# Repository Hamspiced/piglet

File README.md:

# Piglet Wardriver

**Piglet** is an open-source ESP32-based wardriving platform that scans nearby Wi-Fi networks, records GPS position, saves WiGLE-compatible CSV logs to SD, and provides a real-time web UI for control, uploads, and device status.

Designed for **[Seeed XIAO ESP32-S3](https://wiki.seeedstudio.com/xiao_esp32s3_getting_started/), [XIAO ESP32-C5](https://wiki.seeedstudio.com/xiao_esp32c5_getting_started/), [XIAO ESP32-C6](https://wiki.seeedstudio.com/xiao_esp32c6_getting_started/), and [XIAO ESP32-C3](https://wiki.seeedstudio.com/XIAO_ESP32C3_Getting_Started/)**, Piglet focuses on:

- Reliable scanning while in motion  
- Clean WiGLE-ready data collection  
- Simple field deployment  
- Fully hackable open firmware

## Features

- 2.4 GHz Wi-Fi scanning  
- 5 GHz scanning on ESP32-C5 hardware  
- GPS position, heading, and speed logging  
- SD card logging in WiGLE CSV format  
- Web UI for:
  - Start / stop scanning  
  - Upload logs to WiGLE, WDGoWars, and Wardrift  
  - View device status  
  - Manage SD files  
  - Edit configuration  
- OLED live status display  
- Optional battery monitoring (board dependent)  
- Automatic STA connect with AP fallback  
- **Home network auto-return** — detects your home SSID while wardriving, automatically connects and uploads pending CSVs, then resumes wardriving once you drive out of range again
- Optimized for mobile wardriving or warWalking!
- **ESP-Now Mesh Node mode** — pair with a coordinator device for multi-node wardriving
- **Mesh auto-start on boot** — configure `meshModeOnBoot` to automatically enter Core or Node mode after uploads complete, bypassing the AP window
- **Screen rotation** — mount the display upside-down and set `rotateScreen180=true` to flip 180°
- **Auto-start wardriving after uploads** — set `autoStartAfterUpload=true` to disconnect from home Wi-Fi immediately after boot uploads complete and begin scanning without delay
- **PigletNode** — standalone minimal firmware for XIAO ESP32-C5 that boots directly as a mesh node (no display, GPS, or SD required)
- **Wardrive Go BLE bridge** — while on the Mesh Node/Core page, advertise a RocketGod "iosESP" BLE bridge so the Wardrive Go / WarBLE Go phone app can pair and plot APs live on its map
- **Self-update from GitHub Releases** — checks for a newer firmware version at boot and, with one click in the Web UI, downloads and flashes it over the air
- **Core-pushed mesh node OTA updates** — a Piglet acting as Core can push a new firmware image to any connected node (PigletNode, T-Dongle C5, or headless XIAO) over the existing ESP-Now link, no USB required
- **On-device "Update Nodes through Core?" prompt** — a Core's own screen shows a 30-second confirm prompt when a connected XIAO-based node is running mismatched firmware; a single button press confirms the push
- **Auto-update for headless PigletNode nodes** — optional toggle lets a Core silently push firmware to out-of-date headless PigletNode nodes with no on-device confirmation
- **Manual per-node channel-range overrides** — pin a specific mesh node (by MAC) to a fixed channel range from the Web UI instead of the automatic even split

## ESP-Now Mesh Network Node Mode

Piglet includes a built-in **Mesh Node mode** that lets it act as a wireless wardriving node alongside a compatible coordinator device. In this mode, Piglet scans Wi-Fi networks and forwards results over ESP-Now — no SD card or GPS fix required on Piglet itself. The coordinator handles GPS stamping and data logging.

### Compatible Coordinator Devices

- **Biscuit Pro** by [Hedge / Biscuit Shop](https://biscuitshop.us)
- **JCMK C5 Wardriver** by JustCallMeKoko

### How to Use

1. Power on your coordinator device (Biscuit Pro or JCMK C5 Wardriver)
2. On Piglet, press the button to cycle pages until you reach **Mesh Node** (the last page after the pig animation)
3. Piglet automatically searches for a coordinator on ESP-Now channel 6
4. Once connected, it receives a channel range assignment and begins forwarding scan data
5. Press the button again to exit Mesh Node mode and return to normal wardriving

### Mesh Node Display

While in Mesh Node mode the OLED shows:
- Link status (Searching / Core linked)
- Coordinator MAC address
- Assigned channel range
- Total networks discovered
- Records forwarded to the coordinator

> **Note:** Entering Mesh Node mode suspends normal WiGLE CSV logging. All data is sent live to the coordinator. Exiting the page restores normal scanning automatically.

### Auto-Start Mesh Mode on Boot

Set `meshModeOnBoot` in `/wardriver.cfg` to automatically enter mesh mode after boot uploads are complete, without needing to navigate pages manually:

| Value | Behaviour |
|-------|-----------|
| `none` | Normal wardriving (default) |
| `core` | Enters Mesh Core mode — acts as coordinator, logs records from nodes |
| `node` | Enters Mesh Node mode — forwards scan results to a Core |

When `core` or `node` is set the SoftAP window is **skipped entirely** (ESP-Now owns the WiFi stack and the AP would be non-functional). The device goes straight from boot uploads to the mesh page. Set via the web UI **Mesh Mode On Boot** dropdown or directly in `/wardriver.cfg`.

### Wardrive Go BLE Bridge

While on the Mesh Node or Core page, Piglet can advertise a RocketGod "iosESP" BLE bridge (service UUID `47686F73-7445-5350-4272-696467655376`, advertised as `iosESP-XXXX`) so the **Wardrive Go / WarBLE Go** phone app can pair and plot APs live on its map:

- **Node** pushes its own scan finds plus its own GPS fix.
- **Core** pushes every node-forwarded AP plus its own GPS fix.

Enable it with the **Wardrive Go BLE Bridge** toggle in the Web UI's Configuration card (`wardriveGoBridge` in `/wardriver.cfg`, default off). The bridge is only ever active while on the Mesh Node/Core page — it is torn down immediately when you leave it. While enabled, the Mesh page's hold-button hint is replaced with a `WG: off / advertising / connected` status line. Requires the **NimBLE-Arduino** library (see Building Firmware below).

## PigletNode — Standalone Mesh Node

A minimal, standalone firmware for the **Seeed XIAO ESP32-C5** in the `PigletNode/` folder. No display, GPS, or SD card required — flash it and it automatically pairs with any Piglet running in Core mode and begins scanning.

- Single-file Arduino sketch, zero external library dependencies
- Boots directly into JCMK-compatible ESP-Now node mode
- Dual-band scanning: 40 channels (2.4 GHz ch 1–14 + 5 GHz UNII-1/2/2e/3)
- Auto-pairs with Piglet Core mode (XIAO or T-Dongle)
- 30-second Core timeout with automatic re-search
- LED: fast blink = searching, slow blink = paired and scanning
- Hold BOOT button > 2 s to force a re-search

**Flash:** Open `PigletNode/PigletNode.ino` in Arduino IDE, select **XIAO_ESP32C5**, upload. No libraries to install.

## T-Dongle C5 Variant

A standalone firmware port is available for the **LilyGo T-Dongle C5** in the `TDongleC5_Piglet/` folder. This variant is a self-contained single-file sketch with its own display driver, LED control, and web UI — no external OLED required.

**Hardware:** LilyGo T-Dongle C5 (ESP32-C5, built-in ST7735 0.96" TFT, APA102 LED, TF card slot)

**Additional GPS:** Connect any UART GPS module via the Qwiic/JST connector (RX=GPIO12, TX=GPIO11)

**Pages:** Status · Networks · Navigation · Pig animation · Mesh Node

### T-Dongle C5 Required Libraries

Install via Arduino Library Manager (`Sketch → Include Library → Manage Libraries`):

| Library | Author |
|---------|--------|
| Adafruit ST7735 and ST7789 Library | Adafruit |
| Adafruit GFX Library | Adafruit |
| Adafruit BusIO | Adafruit |
| TinyGPSPlus | Mikal Hart |
| ArduinoJson | Benoit Blanchon |
| NimBLE-Arduino | h2zero |

All networking, SPI, SD, ESP-Now, and ESP-IDF headers are included in the ESP32 Arduino core — no separate install needed.

**Board setup:** Add `https://espressif.github.io/arduino-esp32/package_esp32_dev_index.json` to Additional Boards Manager URLs, install **esp32 by Espressif v3.x or later**, and select **ESP32C5 Dev Module**.

## Waveshare ESP32-C5 Touch LCD 3.5 Variant

A self-contained PlatformIO port for the **Waveshare ESP32-C5-Touch-LCD-3.5**
is available in [WaveshareC5_Piglet](WaveshareC5_Piglet/README.md), with ST7796
TFT, FT6336 touch, onboard LC76G GPS, SD logging, and a matching standalone
**XIAO ESP32-C5** mesh node. Hardware dependencies are pinned.

The tested mesh profile is Waveshare Core plus one matching XIAO Node. Its
record acknowledgment/retry extension requires the matching firmware pair;
legacy peers, reverse roles, and multiple nodes are not hardware-qualified.
See the variant's [verification notes](WaveshareC5_Piglet/docs/VERIFICATION.md)
for delivery, recovery, storage tests, and remaining limits.

## Supported Hardware

### Microcontroller Boards

- [Seeed XIAO ESP32-S3](https://www.seeedstudio.com/XIAO-ESP32S3-p-5627.html)  
- [Seeed XIAO ESP32-C5](https://www.seeedstudio.com/Seeed-Studio-XIAO-ESP32C5-p-6609.html) *(required for 5 GHz scanning)*  
- [Seeed XIAO ESP32-C6](https://www.seeedstudio.com/Seeed-Studio-XIAO-ESP32C6-p-5884.html)  
- [Seeed XIAO ESP32-C3](https://www.seeedstudio.com/Seeed-XIAO-ESP32C3-p-5431.html) *(2.4 GHz only, headless — set `board=c3`)*  
- LilyGo T-Dongle C5 *(standalone variant — see above)*
- [Seeed XIAO ESP32-C5](https://www.seeedstudio.com/Seeed-Studio-XIAO-ESP32C5-p-6609.html)  *(PigletNode — mesh node only, see above)*  

### Required Peripherals

- I2C GPS module (ATGM336H)
- 128×64 SSD1306 OLED display (I2C)
- SPI SD card module
- Optional LiPo battery connected to XIAO battery inputs

### Peripheral Sourcing  
You can get everything on Amazon but its pricey.  if you dont mind waiting on aliexpress heres the build list.
- Xiao-C5 - 7$ [SeedStudio](https://www.seeedstudio.com/Seeed-Studio-XIAO-ESP32C5-p-6609.html)
- SSD1306 128x63 OLED - $2 [aliexpress](https://www.aliexpress.us/item/3256805954920554.html)
- ATGM-336h - $3.39 [aliexpress](https://www.aliexpress.us/item/3256809330278648.html)
- SD-Card Module - $1.33 [aliexpress](https://www.aliexpress.us/item/3256808167816573.html)
- User Button - $0.41 [Item:CS1211 From Digikey](https://www.digikey.com/en/products/detail/cit-relay-and-switch/CS1211/16607858)

$14 if you wanted to breadboard it yourself.

## Wiring / Pinouts

Pin mappings are automatically selected by firmware.

### XIAO ESP32-S3

| Function | Pin |
|----------|-----|
| I2C SDA | GPIO 5 |
| I2C SCL | GPIO 6 |
| GPS RX | GPIO 4 |
| GPS TX | GPIO 7 |
| Button | GPIO 1 |
| SD CS | GPIO 2 |
| SD MOSI | GPIO 10 |
| SD MISO | GPIO 9 |
| SD SCK | GPIO 8 |

### XIAO ESP32-C6 / ESP32-C5

| Function | Pin |
|----------|----- |
| I2C SDA | GPIO 23 |
| I2C SCL | GPIO 24 |
| GPS RX | GPIO 12 |
| GPS TX | GPIO 11 |
| Button | GPIO 0 |
| SD CS | GPIO 7 |
| SD MOSI | GPIO 10 |
| SD MISO | GPIO 9 |
| SD SCK | GPIO 8 |

**Note:** Only the ESP32-C5 supports 5 GHz Wi-Fi scanning.

### XIAO ESP32-C3

Set `board=c3` in `/wardriver.cfg` or select **XIAO C3** in the Web UI. Auto-detected from chip model on first boot.

| Function | Pin |
|----------|----- |
| I2C SDA | GPIO 6 (D4) |
| I2C SCL | GPIO 7 (D5) |
| GPS RX | GPIO 20 (D7) |
| GPS TX | GPIO 21 (D6) |
| Button | *none* (GPIO 9 = SPI MISO conflict — wire externally if needed) |
| SD CS | GPIO 2 (D0) |
| SD MOSI | GPIO 10 (D10) |
| SD MISO | GPIO 9 (D9) |
| SD SCK | GPIO 8 (D8) |

**Note:** 2.4 GHz only. No built-in display — attach an optional SSD1306 OLED on D4/D5.

## 3D Printed Cases

Print-ready STL files are available in the `Case Files/` directory. These cases are designed specifically for the Piglet PCB and module stack.

### 👏 Case Design by Bread — Breadbox Systems

The Piglet case was designed by **Bread** at [Breadbox Systems](https://breadboxsystems.com). If you print one, please take a moment to **like and boost the design on MakerWorld** — it helps the creator and makes the design easier for others to find.

> **[🖨️ Print the Piglet Wardriver Case on MakerWorld →](https://makerworld.com/en/models/2708429-piglet-wardriver-case#profileId-3000037)**

| File | Description |
|------|-------------|
| `Piglet Face.STL` | Front panel / lid |
| `Piglet Butt.STL` | Rear enclosure |
| `Piglet Butt with SMA hole.STL` | Rear enclosure with external antenna cutout |
| `Piglet Midboard.STL` | Internal standoff / mid-layer |
| `Piglet Features.stl` | Feature plate / accessory mount |

For the **T-Dongle C5** variant, GPS antenna mount STLs are included in `TDongleC5_Piglet/GPS STL/`.

> Print with standard PLA or PETG. No supports required on most parts. Recommend 0.2 mm layer height, 3 perimeters.

## PCB Design

Piglet includes custom PCB designs for compact, production-ready builds. KiCad project files and Gerber production files are available in the `PCB Files/` directory.

### PCB Images

| Board Front | Board Back | Board Close-up |
|-------------|------------|----------------|
|  |  |  |

### Assembled Piglet

| Module Arrangement | Front View | Back View |
|--------------------|------------|----------|
|  |  |  |

**Assembly Note:** When stacking modules, apply **Kapton tape** between components to prevent electrical shorts. Pay special attention to exposed pins and solder joints that may contact adjacent modules.

## First Time Run Initialization

The Wardriver functions using a config file located on the root of a FAT32-formatted SD card. On first boot the device will start its own access point (`Piglet-WARDRIVE` / `wardrive1234`) so you can connect and fill in your settings via the web interface — or you can place the config file on the SD card manually before powering on.

**AP Timer & Keep-Alive**

The SoftAP runs for **60 seconds** by default. About **30 seconds before** that window expires, the WebUI shows a *"Stay in WebUI?"* prompt — clicking **Stay** extends the window to a **5 minute** rolling timer so you have room to actually use the WebUI. The same prompt re-appears 30 seconds before the 5 minute timer expires; clicking Stay again resets it.

- **Stay** — extends (or re-extends) the window to 5 minutes.
- **Start Scanning Now** — closes the AP immediately and begins wardriving.
- **Ignored / browser closed** — timer runs out, AP closes, scanning starts.

The OLED shows the live countdown (`AP: 192.168.4.1 60s` initially, `m:ss` once extended). Once your home Wi-Fi is configured, the device will connect to it on subsequent boots and the WebUI is reachable on the STA IP shown on the OLED — the AP only comes up if STA fails.

**Location:** `/wardriver.cfg` on the SD card root

A sample config file is included in `Arduino Files/Piglet/wardriver.cfg`. The full default config with all available keys is shown below:

```ini
# ============================================================
# Piglet Wardriver Configuration
# Format: key=value
# Lines starting with # are comments and ignored.
# ============================================================

# ------------------------------------------------------------
# WiGLE Upload
# ------------------------------------------------------------
# Use only the "Encoded for Use" token from wigle.net/account
# Leave empty to disable WiGLE uploads.

wigleBasicToken=EnterWigleTokenHere

# ------------------------------------------------------------
# WDGoWars
# ------------------------------------------------------------
# Get your API key at: https://wdgwars.pl/profile/
# Leave empty to disable WDGoWars uploads.

wdgwarsApiKey=EnterWDGoWarsAPIKeyHere

# ------------------------------------------------------------
# Wardrift
# ------------------------------------------------------------
# Get your API key at: https://wardrift.net
# Leave empty to disable Wardrift uploads.

wardriftApiKey=EnterWardriftAPIKeyHere

# ------------------------------------------------------------
# Max Automatic Uploads at Boot
# ------------------------------------------------------------
# -1 = Upload ALL pending files every boot
#  0 = Disabled — no auto-upload at boot (use web UI manually)
# 1+ = Upload up to N files per boot

maxBootUploads=-1

# ------------------------------------------------------------
# Device Name (optional)
# ------------------------------------------------------------
# A short label for this device. Used in WiGLE CSV filenames
# and in the WiGLE upload header so you can tell devices apart.
# Spaces become underscores. Max 20 characters.
# Leave empty to use the default (no prefix).

deviceName=

# ------------------------------------------------------------
# Home Wi-Fi (STA mode)
# ------------------------------------------------------------
# If provided, device connects on boot.
# If connection fails, falls back to SoftAP for 60 seconds
# (can be extended via the "Stay in WebUI?" prompt that appears
# ~30 s before the timer expires).
#
# Auto-return while wardriving: if this SSID is seen in a scan result
# while driving, the device stops scanning, connects to it, and uploads
# pending CSVs automatically (same upload flow as boot) -- no need to
# reboot or stop by the web UI when you get home. Normal wardriving
# resumes automatically once the connection is lost (e.g. driving back
# out of range).

homeSsid=EnterWifiHere
homePsk=EnterWifiPasswordHere

# ------------------------------------------------------------
# Wardriver Access Point (SoftAP fallback)
# ------------------------------------------------------------
# SSID and password for the temporary config AP.
# Password must be 8+ characters or AP becomes open.

wardriverSsid=Piglet-WARDRIVE
wardriverPsk=wardrive1234

# ------------------------------------------------------------
# GPS Settings
# ------------------------------------------------------------
# UART baud rate for the GPS module.
# Common values: 9600, 38400, 115200

gpsBaud=9600

# ------------------------------------------------------------
# Wi-Fi Scan Mode
# ------------------------------------------------------------
# aggressive  — scans every ~3 seconds using async mode (faster, more power)
# powersaving — scans every ~12 seconds (slower, less power)

scanMode=aggressive

# ------------------------------------------------------------
# Speed Units (display only)
# ------------------------------------------------------------
# kmh = kilometers per hour
# mph = miles per hour

speedUnits=mph

# ------------------------------------------------------------
# Battery Test
# ------------------------------------------------------------
# true = logs elapsed time on battery to /battery_test.csv
# false = disabled

batteryTest=false

# ------------------------------------------------------------
# Mesh Mode On Boot
# ------------------------------------------------------------
# Automatically enter ESP-Now mesh mode after boot uploads complete.
# Bypasses the SoftAP window and jumps directly to the mesh page.
#
#   none = Normal wardriving mode (default)
#   core = Start as Mesh Core (coordinator) — logs data from nodes
#   node = Start as Mesh Node — forwards scan results to a Core
#
# Requires a compatible coordinator (Biscuit Pro, JCMK C5 Wardriver)
# when using node mode.

meshModeOnBoot=none

# ------------------------------------------------------------
# Screen Rotation
# ------------------------------------------------------------
# Rotate the display 180 degrees for upside-down mounting.
# Values: true or false
# Reboot required after changing.

rotateScreen180=false

# ------------------------------------------------------------
# Auto-Start Wardriving After Uploads
# ------------------------------------------------------------
# When true: disconnects from home Wi-Fi immediately after boot uploads
# complete and begins wardriving without delay. The web UI remains
# accessible if you later connect to the Wardriver AP, but the device
# will not hold the STA link open.
# Values: true or false
# Reboot required after changing.

autoStartAfterUpload=false

# ------------------------------------------------------------
# SD Card SPI Clock Ceiling
# ------------------------------------------------------------
# Boot negotiates the fastest SD-over-SPI clock (descending ladder) up to
# this cap and uses the fastest speed that mounts successfully. Lower this
# if you see SD write errors/corruption on marginal wiring (e.g. long
# breadboard jumpers). Default is a commonly-safe ceiling for SD-over-SPI.
# Reboot required after changing.

sdMaxSpiHz=20000000

# ------------------------------------------------------------
# Network Whitelist
# ------------------------------------------------------------
# Up to 10 SSIDs that will never be written to the WiGLE CSV log.
# Matching is exact and case-sensitive; empty slots never match, so
# blank/hidden SSIDs are never accidentally filtered. Whitelisted
# networks are still scanned and still count toward the Found totals —
# they are simply skipped when writing log rows. Editable from the
# web UI's Configuration card ("Network Whitelist" textarea, one SSID
# per line) or directly in this file.

ssidWhitelist1=
ssidWhitelist2=
ssidWhitelist3=
ssidWhitelist4=
ssidWhitelist5=
ssidWhitelist6=
ssidWhitelist7=
ssidWhitelist8=
ssidWhitelist9=
ssidWhitelist10=

# ------------------------------------------------------------
# Wardrive Go BLE Bridge
# ------------------------------------------------------------
# When true, the Mesh Node/Core page advertises a RocketGod "iosESP" BLE
# bridge (as iosESP-XXXX) so the Wardrive Go / WarBLE Go phone app can pair
# and plot APs live. Only active while on the Mesh Node/Core page.
# Values: true or false

wardriveGoBridge=false

# ------------------------------------------------------------
# Auto-Update Headless PigletNode Nodes (Core mode)
# ------------------------------------------------------------
# When true, a Core silently pushes staged /Firmware/PigletNode.ota.bin to
# any connected headless PigletNode running different firmware -- no
# on-device confirmation, since those nodes have no screen. XIAO-based
# nodes (Piglet/TDongleC5_Piglet) always use the on-screen confirm prompt
# instead, regardless of this setting. Recommended: use an SD card rated
# at least 16GB for sustained-write reliability.
# Values: true or false

autoUpdateHeadlessNodes=false
```

### Auto-Start Wardriving After Uploads — How to Disable

> **Important:** When `autoStartAfterUpload=true`, the device disconnects from your home Wi-Fi immediately after uploads finish and goes straight into wardriving. Because it no longer holds the STA connection, the web UI is **not** reachable on your home network after boot.

To disable this setting after it has been enabled, you have two options:

**Option 1 — Connect via the Wardriver AP**

When Piglet is away from the saved home network (or the home network is unavailable), it falls back to its own SoftAP. Connect to it and use the web UI:

1. Power on the device somewhere the home Wi-Fi is not in range (or temporarily forget the home network on the device by clearing `homeSsid` in the config)
2. Connect your phone or laptop to the **Wardriver SSID** (default: `Piglet-WARDRIVE` / `wardrive1234`)
3. Open a browser and go to **`http://192.168.4.1`**
4. In the **Configuration** section, set **Auto-Start Wardriving After Uploads** to **Disabled**
5. Click **Save & Reboot**

**Option 2 — Edit the SD card directly**

1. Remove the SD card from the device
2. Open `wardriver.cfg` in any text editor
3. Change `autoStartAfterUpload=true` to `autoStartAfterUpload=false`
4. Save the file, re-insert the SD card, and reboot

## Button Functions

### Press Types

| Press | Timing | Action |
|-------|--------|--------|
| **Single press** | Quick tap | Advance to next page |
| **Double press** | Two taps within 350 ms | Toggle scan pause *(Status page)* / toggle Wardrive Go BLE bridge *(Mesh Node page)* |
| **Long press** | Hold ≥ 2 seconds | Enter deep sleep *(or toggle Core/Node on the Mesh Node page)* |
| **Single press** *(while sleeping)* | Any | Wake from deep sleep / reboot |

### Pages (Single Press cycles through these)

| Page | Name | What it Shows | Scanning |
|------|------|---------------|----------|
| 0 | **Status** | Scan state, SD, GPS fix, WiFi, network counts, speed, IP, upload status | ✅ Active |
| 1 | **Networks** | Large display of 2.4 GHz, 5 GHz, and total network counts | ✅ Active |
| 2 | **Navigation** | Compass arrow, heading direction, current speed | ✅ Active |
| 3 | **Paused** | Pause icon — scanning fully stopped | ❌ Paused |
| 4 | **Pig** | Walking pig animation 🐷 | ✅ Active |
| 5 | **Mesh Node** | ESP-Now link state, coordinator MAC, channel range, Found/Sent counts | ↔ Forwarded via ESP-Now |

### Double Press — Status Page Only

When on the **Status page**, double-pressing toggles a scan pause without leaving the page. Useful for a quick stop without navigating to the Pause page.

- **Double press →** Scanning paused on status page
- **Double press again →** Scanning resumed
- **Single press (page change) →** Pause automatically cleared when leaving page 0

### Long Press — Deep Sleep

Hold the button for **2 seconds** from any page:
- Active log file is flushed and closed before sleeping
- OLED displays `Sleep...` then powers off
- A single button press wakes the device (full reboot)

### Mesh Node Page

Entering **page 5** automatically starts ESP-Now node mode. Leaving it (single press to advance) automatically restores normal wardriving. See the [ESP-Now Mesh Network Node Mode](#esp-now-mesh-network-node-mode) section above for details.

While on this page, **double-pressing** toggles the Wardrive Go BLE bridge on/off immediately (no reboot or page re-entry needed) and saves the new state to `/wardriver.cfg`, so it stays on for this page on future boots too — the same effect as flipping the Web UI's **Wardrive Go BLE Bridge** toggle and saving. See [Wardrive Go BLE Bridge](#wardrive-go-ble-bridge) above.

When acting as **Core** and a connected XIAO-based node has mismatched firmware, the page instead shows an **"Update Nodes through Core?"** confirm prompt; a single press on that page confirms the push (instead of advancing to the next page) for as long as the prompt is showing. See [Firmware Updates](#firmware-updates-v30) below.

## Building Firmware

### Requirements

- **Arduino IDE 2.x** or **PlatformIO**
- **Arduino-ESP32 core v3.3.10** — this is the exact version used to build official releases (see `.github/workflows/release-firmware.yml`) and the version this project is tested against. In Arduino IDE's Boards Manager, select version **3.3.10** specifically from the dropdown before installing (it keeps multiple versions installable side by side).
  > **Known issue:** ESP32 Arduino core **3.3.11 and 3.3.12** introduce a regression on the XIAO ESP32-C5's native USB that breaks the normal auto-reset-into-bootloader sequence — uploads from Arduino IDE will silently fail to connect unless you manually hold **BOOT**, tap **RESET**, then release **BOOT**. If you're hitting this, downgrade to core **3.3.10** via Boards Manager; it resolves the issue with no other changes needed.

### Required Libraries — XIAO Variant (S3 / C5 / C6)

Install via Arduino Library Manager (`Sketch → Include Library → Manage Libraries`):

| Library | Author | Notes |
|---------|--------|-------|
| TinyGPSPlus | Mikal Hart | GPS NMEA parsing |
| Adafruit GFX Library | Adafruit | Graphics dependency |
| Adafruit SSD1306 | Adafruit | OLED display driver |
| Adafruit BusIO | Adafruit | Required by SSD1306 |
| ArduinoJson | Benoit Blanchon | v6.x or v7.x |
| NimBLE-Arduino | h2zero | Wardrive Go BLE bridge on the Mesh page |

All other headers (`WiFi`, `WebServer`, `WiFiClientSecure`, `HTTPClient`, `SD`, `SPI`, `Wire`, `esp_now.h`, `esp_wifi.h`) are included in the ESP32 Arduino core — no separate install needed.

### Required Libraries — T-Dongle C5 Variant

Install via Arduino Library Manager:

| Library | Author | Notes |
|---------|--------|-------|
| Adafruit ST7735 and ST7789 Library | Adafruit | TFT display driver |
| Adafruit GFX Library | Adafruit | Graphics dependency |
| Adafruit BusIO | Adafruit | Required by ST7735 |
| TinyGPSPlus | Mikal Hart | GPS NMEA parsing |
| ArduinoJson | Benoit Blanchon | v6.x or v7.x |
| NimBLE-Arduino | h2zero | Wardrive Go BLE bridge on the Mesh page |

All networking, SPI, SD, ESP-Now, and ESP-IDF headers are built into the ESP32 core.

### Flash Steps

1. Select the correct **XIAO ESP32 board** variant (S3, C5, or C6)
2. **CRITICAL:** Enable **PSRAM** (required for TLS/HTTPS uploads)
   - Tools → PSRAM → **OPI PSRAM** (C5/C6) or **QSPI PSRAM** (S3)
3. Use the **`8M with spiffs (3MB APP/1.5MB SPIFFS)`** partition scheme — this gives two OTA app slots, required for self-update and Core-pushed mesh node updates (v3.0+). Boards still on the old **Huge APP (3MB No OTA)** scheme need one more reflash with this scheme to gain OTA capability.
4. Upload firmware (see the **Known issue** note above if the board won't auto-reset into bootloader mode on upload)
5. Insert **FAT32-formatted SD card**  
6. Add `/wardriver.cfg` to SD card root with your WiGLE API key and WiFi credentials
7. Restart device with RST button or power cycle

### Firmware Updates (v3.0+)

Every board can check GitHub Releases for a newer firmware version and install it over the air, and a Piglet acting as mesh Core can push updates out to connected nodes of any board type.

**Self-update (per device):**
1. At boot, if connected to the home network, the device checks `github.com/Hamspiced/piglet` releases for a newer version and shows the result in the Web UI's **Firmware Update** card.
2. Click **Install Update** — the device downloads its own firmware image over HTTPS and flashes it via the ESP32's native OTA mechanism, then reboots automatically.
3. In the same pass, it also downloads the other two boards' images to `/Firmware/` on the SD card, so a Core can immediately push them to connected nodes (see below).

**Core-pushed mesh node updates:**
- A Piglet acting as Core reads `/Firmware/<Board>.ota.bin` files from its SD card at boot (one file per board type: `Piglet.ota.bin`, `TDongleC5_Piglet.ota.bin`, `PigletNode.ota.bin`).
- The Web UI's **Mesh Nodes** panel (shown only in Core mode) lists connected nodes with an **Update** button; clicking it streams the matching image to that node over the existing ESP-Now link — no USB needed.
- Every node reports its firmware version to the Core on each discovery handshake and heartbeat. When a connected **XIAO-based** node (Piglet or TDongleC5_Piglet) is running mismatched firmware, the Core's own screen shows an **"Update Nodes through Core?"** prompt with a 30-second countdown; a single button press on that page confirms the push instead of advancing to the next page, and letting it time out skips that node for the rest of the session. Multiple mismatched nodes queue and are pushed one at a time, with live progress shown on-screen.
- Headless **PigletNode** nodes have no screen, so they're never prompted. Enable the **Auto-Update Headless PigletNode Nodes** Web UI toggle (`autoUpdateHeadlessNodes`, default off) to have the Core silently push staged firmware to them instead, retried at most once per node per session. Recommended for use with an SD card rated at least 16GB for sustained-write reliability.
- The **Store Piglet Node Firmware** button (Firmware Update card) downloads the latest `PigletNode.ota.bin` release asset to `/Firmware/` on demand — this works even when the Core's own firmware is already current, unlike the self-update check above which only resolves release assets when a *newer* version is found.
- The node verifies a SHA-256 of the whole image before switching its boot partition, so an interrupted or corrupted transfer leaves it running its old firmware.
- A board-type marker prevents accidentally pushing the wrong board's image (e.g. a T-Dongle image to a bare PigletNode) even though every Piglet variant shares the same ESP32-C5 silicon.
- `/Firmware/` can also be populated manually (copy a release's `.ota.bin` assets onto the SD card) for offline/no-home-network setups.
- The Web UI's Mesh Nodes card also has a **Channel Overrides** panel: pin a specific node (by MAC) to a fixed channel range instead of the automatic even split — useful for a node with a directional antenna aimed at a specific band. Persisted to `/mesh_channel_overrides.cfg` on the Core's SD card.

**Security note:** image integrity is checked via SHA-256 (corruption/truncation), not a cryptographic signature (authenticity) — this matches the trust model of the rest of Piglet's ESP-Now mesh, which has no built-in authentication either.

### Where to Order

I always order everything from JLCPCB because i get the best deals.  However i do understand that people prefer the all in one project offers of PCBway so i have created this project here:

[PCBWayProjects](https://www.pcbway.com/project/shareproject/Piglet_Opensource_Wardriving_Project_1a21b94b.html)

## License

Creative Commons Attribution-NonCommercial 4.0 (CC BY-NC 4.0)

You may:

- Use  
- Modify  
- Share  

You may **not** use this project for commercial purposes.

https://creativecommons.org/licenses/by-nc/4.0/

---

Created by **Midwewest Gadgets LLC**

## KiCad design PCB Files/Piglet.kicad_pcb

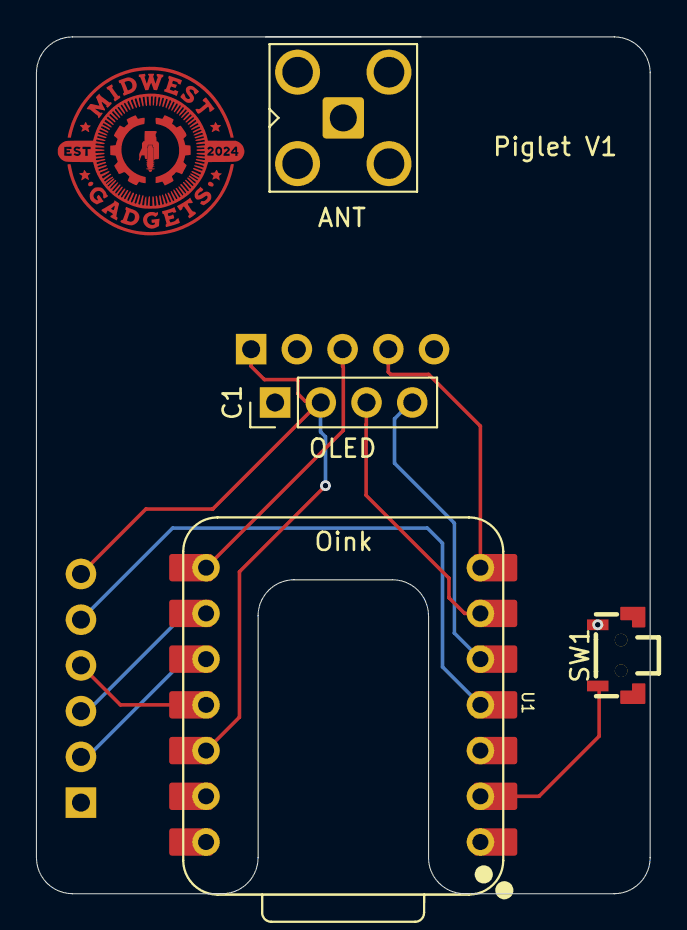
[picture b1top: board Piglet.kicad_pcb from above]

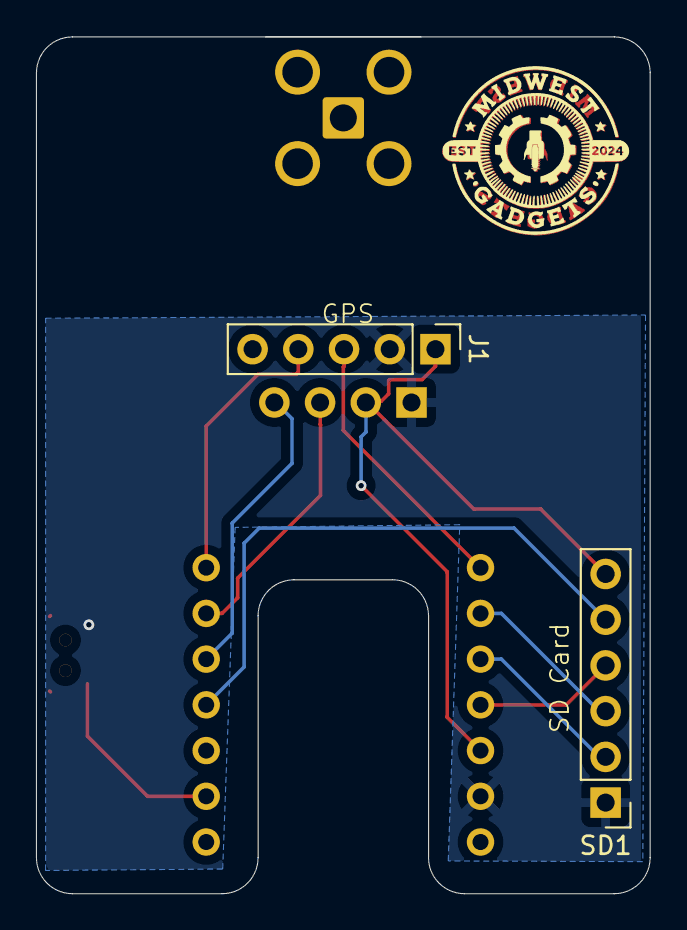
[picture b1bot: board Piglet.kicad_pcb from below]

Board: 2 copper layers, 34.1 x 47.6 mm, 6 parts (2 on the bottom side), 11 nets.

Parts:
ANT: SMA_Amphenol_901-143_Horizontal
C1: SSD1306 128x64; PinHeader_1x04_P2.54mm_Vertical
J1: Conn_01x05_Pin; PinHeader_1x05_P2.54mm_Vertical
SD1: Conn_01x06_Pin; PinHeader_1x06_P2.54mm_Vertical
SW1: SW_Push; SW-SMD_TS24CA
U1: XIAO-ESP32-C6-SMD; XIAO-ESP32-C6-DIP

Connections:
+3V3: C1.2 (VCC), J1.5, SD1.6, U1.12 (3V3)
CS: SD1.5, U1.4 (GPIO21_D3)
D1: SW1.1, U1.2 (GPIO1_A1_D1)
GND: C1.1 (GND), J1.4, SD1.1, SW1.2, U1.13 (GND)
Mosi: SD1.4, U1.11 (GPIO18_D10_MOSI)
RX: J1.2, U1.7 (GPIO16_D6_TX)
TX: J1.3, U1.8 (GPIO17_D7_RX)
clk: SD1.3, U1.9 (GPIO19_D8_SCK)
miso: SD1.2, U1.10 (GPIO20_D9_MISO)
scl: C1.3 (SCL), U1.6 (GPIO23_D5_SCL)
sda: C1.4 (SDA), U1.5 (GPIO22_D4_SDA)

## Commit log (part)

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2026-02-19 Revise README for Piglet wardriving platform
    Updated README to enhance clarity and detail about Piglet wardriving platform, including features, supported hardware, configuration, and building instructions.
2026-02-20 v1.0-beta: Initial release with modular refactor and new features
    Major Refactor:
    - Split monolithic Piglet.ino (~2970 lines) into 10 module pairs (.h/.cpp)
    - Modules: Globals, Config, Dedup, GPS, SDUtils, Display, WiFiManager, Scanner, WigleUpload, WebUI
    - Slim entry point in Piglet.ino (~393 lines) with setup(), loop(), and button handler
    - Preserved all existing functionality with zero logic changes
    New Features:
2026-02-20 Change board selection to auto in wardriver.cfg
    Updated board selection to auto in wardriver.cfg
2026-02-20 Update license to CC BY-NC-SA 4.0, add battery test utility
    - Replace CC0 license with CC BY-NC-SA 4.0 in LICENSE file
    - Update README license section to match
    - Add battery_test.h/.cpp for battery endurance testing (disabled by default)
    - Wire battery test into Piglet.ino as commented-out hooks
2026-02-20 Update README.md
    added parts list
2026-02-20 Revise Peripheral Sourcing section in README
    Updated the Peripheral Sourcing section with additional details and formatting.
2026-02-20 Firmware v1.1: Multi-page OLED display with button navigation
    - Add 5-page OLED system: Status, Networks, Navigation, Pause, Pig animation
    - Single press cycles pages, double press toggles scan pause on status page, long press enters deep sleep
    - Page-aware scanning: always active on Networks/Nav/Pig pages, respects AP/STA state on Status page, paused on Pause page
    - Redesigned pig animation with filled cartoon graphics
    - Add GPS signal indicator (X / 1-6 sat bars) to Nav page header
    - Fix compass arrow overlapping direction text on Status and Nav screens
2026-02-20 Add .gitignore and remove tracked .DS_Store
    - Ignore .DS_Store, .zip files, and AGENTS.md
    - Remove Arduino Files/.DS_Store from tracking
2026-02-27 v1.4-beta: Add configurable battery test feature
    Features:
    - Battery test now configurable via wardriver.cfg and web UI
    - New 'batteryTest' config option (true/false) to enable/disable elapsed time logging
    - Battery test logs runtime to /battery_test.csv (no battPin dependency required)
    Improvements:
    - Enhanced wardriver.cfg with descriptive comments for all config values
2026-02-27 Add PCB production Gerber files (Piglet_V1.zip)
2026-03-05 Add PCB and assembly documentation with images
    Added Sections:
    - PCB Design section with board images (Board1-3.jpg)
    - Assembled Piglet section with module arrangement and build photos
    - Assembly note about Kapton tape to prevent shorts
    Images Added:
    - Board1.jpg, Board2.jpg, Board3.jpg (PCB views)
2026-04-23 Release 2.0 - Mesh Node mode, T-Dongle C5 variant, 3D printed cases
    ESP-Now Mesh Network Node Mode
    - New page 5 (XIAO) / page 4 (T-Dongle C5) activated after pig animation
    - Compatible with Biscuit Pro by Hedge and JCMK C5 Wardriver as coordinator
    - Broadcasts discovery request on ESP-Now ch 6, accepts channel assignments
    - Scans assigned channel range and forwards BSSID/SSID/security/RSSI records
    - Periodic heartbeat keeps coordinator link alive
2026-04-23 README: expand button reference and split library tables by variant
2026-04-27 Revision 2.1 - WDGoWars integration, upload improvements, ESP-Now fixes, web Save & Reboot
    WDGoWars Upload Integration (both XIAO and T-Dongle C5)
    - New wdgwarsApiKey config field; set via wardriver.cfg or web UI
    - Uploads CSVs to wdgwars.pl before WiGLE on each boot when key is present
    - POST /api/upload-csv with X-API-Key header; reads server response body
    and prints merged_samples count to serial on success
    - Web UI: WDGoWars card with Test API Key + Upload All CSVs buttons
2026-04-27 Fix T-Dongle compile error; add Get API Key links and API key help text
2026-04-27 Update Piglet Face.STL case file
2026-04-27 README: rename Configuration File to First Time Run Initialization, add full default config
2026-04-28 Fix web delete stalling and empty CSV cleanup
    - Remove blocking wigleLoadHistory() from handleFiles(); it was making a
    15-second HTTPS call on every file-list and delete request
    - Stamp wigleHistoryLastLoadMs on all failure paths in wigleLoadHistory()
    so failed calls don't keep retrying on every files.json request
    - Add standalone deleteEmptyCsvs() called at every boot to purge header-only
    CSVs regardless of whether uploads are configured
2026-04-28 Remove WiGLE upload history stats feature
    The wigleLoadHistory() function made a blocking 15-second HTTPS call
    which was causing file-list and delete requests to stall. The feature
    was unreliable due to file size matching issues and the fundamental
    conflict between blocking network calls and the single-threaded web
    server.
    Removed:
2026-04-29 Add deviceName config key for WiGLE header and filename differentiation
    Both XIAO and T-Dongle C5 variants now support a deviceName= key in
    wardriver.cfg (and the web UI config form).
    When set, the device name:
    - Is appended to the WiGLE CSV header device field:
    XIAO: device=Piglet-{name}
    T-Dongle: device=Piglet-TDongle-{name}
2026-04-29 Fix web UI inaccessible: increase handleStatus JSON buf; remove duplicate log print
    StaticJsonDocument<1024> in handleStatus was too small after adding
    wdgwarsApiKey, deviceName, and maxBootUploads to the config block.
    Overflowed ArduinoJson silently discards fields and sends truncated JSON;
    the browser stalls on the broken response, making the page appear
    inaccessible. Increased to 2048.
    Also removed a duplicate Serial.println before startWebServer() in
2026-04-29 Fix web UI crash: StaticJsonDocument -> DynamicJsonDocument in handlers
    StaticJsonDocument<N> puts N bytes on the Arduino loop task stack (8192B
    total). handleFiles used 4096B and handleStatus used 2048B -- together with
    the WebServer call chain overhead (~2KB) this blew the stack limit, causing
    silent crashes and connection resets whenever the browser fetched either
    endpoint.
    Switched both to DynamicJsonDocument which allocates from the heap
2026-04-29 Add /ping endpoint + handleRoot debug prints for web server diagnostics
2026-04-29 Scanner: async scanning with reduced dwell time for both variants
    Switch both the XIAO (Scanner.cpp) and T-Dongle (TDongleC5_Piglet.ino)
    from blocking WiFi.scanNetworks() to async mode. This keeps GPS parsing,
    the web server, and the display running uninterrupted during the ~1.3s
    radio sweep.
    Changes:
    - async=true on WiFi.scanNetworks() — main loop no longer blocked
2026-04-29 Web UI: add Delete All Logs button to SD Card Files section
    Adds a POST /deleteAll endpoint and a red 'Delete All Logs' button
    above the file list on both the XIAO and T-Dongle web interfaces.
    - Deletes all files in /logs and /uploaded
    - Skips the currently active log file (keeps recording)
    - Returns JSON {ok, deleted} with count of removed files
    - Button uses the existing btn-danger style; browser confirms before
2026-04-29 Add firmware version v2.2 to splash screens and web UI subtitles
2026-04-29 Web UI: rename 'log' badge to 'Not Uploaded' with red styling
2026-04-29 Web UI: add Download All as a ZIP file
    Adds GET /downloadAll to both variants, streaming all CSV files from
    /logs and /uploaded as a single piglet_logs.zip download.
    Implementation details:
    - STORE (no compression) ZIP with data descriptors (flag bit 3)
    - CRC32 computed on-the-fly using a compact 16-entry nibble table
    - Content-Length set upfront from file sizes so the browser shows progress
2026-04-29 Add WebUI keep-alive
    The 60 second AP timer was kicking us out of the WebUI before we could finish anything. Now there's a "Stay in WebUI?" prompt that pops up about 30 seconds before the timer expires — clicking **Stay*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
    **Changes**
    - Added a 5 minute extended AP window that the user opts into via the prompt (no silent auto-extend).
    - Added `/extend` endpoint to reset the 5 minute timer when **Stay** is clicked.
    - `/start` (Start Scan button) now force-closes the AP immediately and begins scanning, even mid-window.
    - `status.json` exposes `apActive`, `apExtended`,
2026-04-29 README: add deviceName config key, fix scanMode timing (async v2.2)
2026-04-29 Add CREDITS.md with attribution for JCMK mesh protocol and dagnazty PR
2026-04-29 README: shoutout to Bread / Breadbox Systems for the Piglet case design
2026-04-30 Bump version to v2.3
2026-04-30 Bump remaining files to v2.3
2026-04-30 Fix Core ADMIN delivery: periodic resend + inter-send gap
    When a node is mid-scan (blocking WiFi.scanNetworks across all channels),
    any ESP-Now packet sent by the Core on ch6 is silently dropped. This caused
    the first connected node to retain its 'all channels' assignment after a
    second node joined, since it missed the narrowed-range ADMIN.
    Two fixes:
    1. coreReassignChannels(): add delay(10) between sends to prevent
2026-04-30 Fix mesh: clear apWindowActive on node/core entry to prevent ESP-Now kill
    stopAPIfAllowed() calls WiFi.disconnect(true,true) when the 60s AP window
    expires, which hard-resets the WiFi driver and silently kills the ESP-Now
    receive callback. If this fires while on the mesh page the Core stops seeing
    CORE_REQUESTs (coreNodeCount stays 0 / 'Waiting for nodes') even though
    nodes still show 'Core linked' from before the reset.
    Fix: set apWindowActive=false in enterNodeMode() and enterCoreMode() for
2026-04-30 Mesh: 45s node timeout + guaranteed post-scan heartbeat (from JCMK analysis)
    JCMK's ESP32DualBandWardriver uses per-channel async scanning (80ms/ch),
    returning to ch 6 between every channel. Piglet does a blocking scan of
    all 40 channels (~3-5s) which delays the 5s heartbeat timer by the full
    scan duration, leaving only ~2 heartbeat windows in the 20s timeout.
    Short-term fixes from reviewing JCMK's runAdminWindowAfterScanCycle():
    1. CORE_NODE_TIMEOUT: 20s -> 45s to account for blocking scan latency
2026-04-30 docs: remove network de-duplication from features list
2026-05-03 feat: Biscuit Node compatibility in Core mode
    Root cause: Biscuit Node drops any ESP-Now packet < 212 bytes
    (sizeof(enow_text_msg_t)), while Piglet was sending 5-byte CORE_REPLY,
    9-byte heartbeats, and variable-length TEXT — all silently dropped.
    Changes:
    - coreSendReply: use full jcmk_text_msg_t (212 bytes) for CORE_REPLY.
    JCMK nodes only check len >= 5, so backward-compatible.
2026-05-04 docs: fix XIAO wardriver.cfg header, add board key, update mesh node comment
2026-05-04 fix: meshModeOnBoot — skip STA/AP entirely for mesh boots, unconditional mesh entry
    Corrects two wrong assumptions from the previous fix:
    1. meshModeOnBoot=node/core should ALWAYS enter mesh mode unconditionally,
    regardless of WiFi availability. These are dedicated mesh devices.
    2. When meshModeOnBoot is set, the 12-second STA connect attempt is
    skipped entirely — no timeout waste on a dedicated mesh node/core.
    The AP window is also skipped. enterNodeMode/enterCoreMode handle
2026-05-06 fix: disable auto-reconnect on STA disconnect to unblock WiFi scanning
    When home WiFi was connected at boot (staOk=true), setAutoReconnect was
    never called. After driving out of range the ESP32 WiFi stack silently
    started background reconnection attempts, which ran concurrently with
    WiFi.scanNetworks(). This caused scans to return 0 results while the
    play indicator showed active — displaying zeros and logging nothing.
    Fix: handleStaTransitions() now calls setAutoReconnect(false) +
